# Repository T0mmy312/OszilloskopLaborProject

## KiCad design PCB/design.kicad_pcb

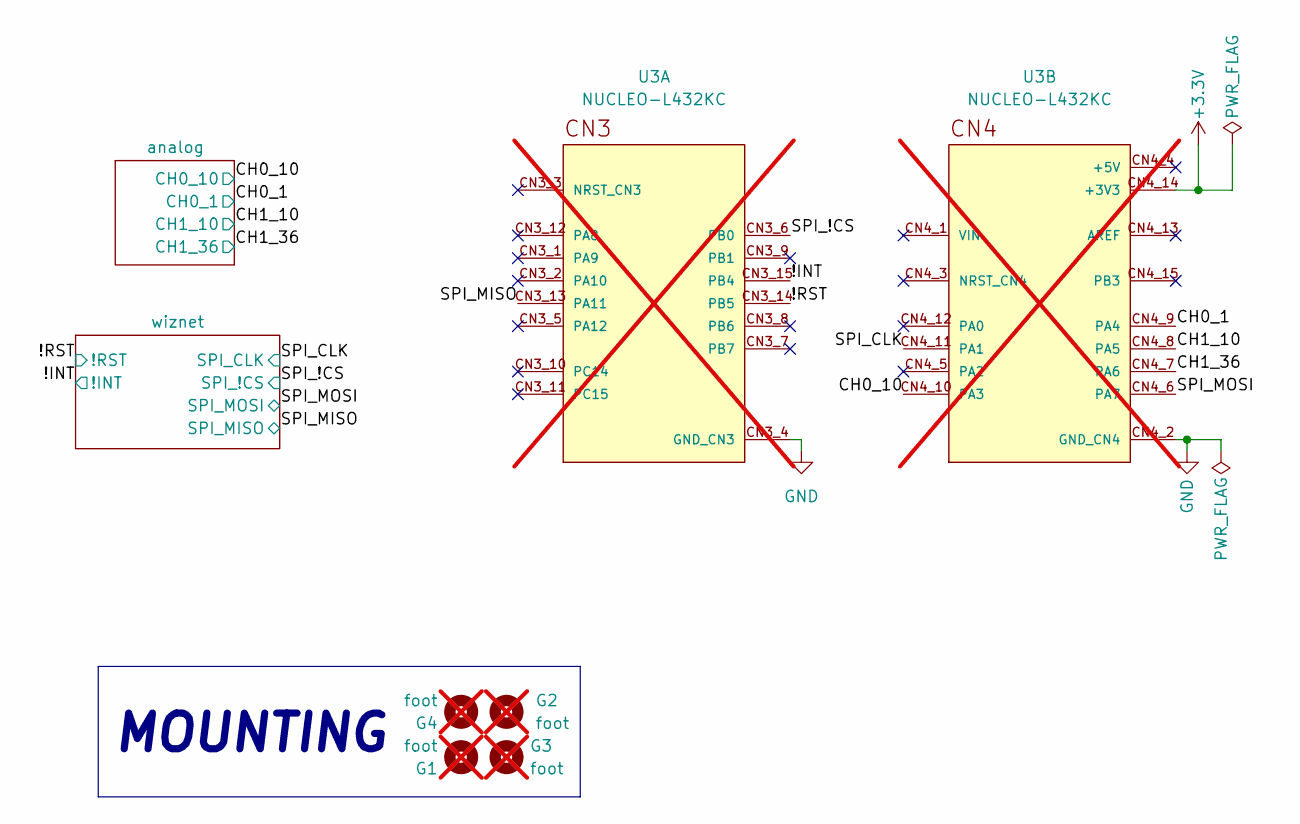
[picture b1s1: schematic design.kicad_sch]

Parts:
G1, G2, G3, G4: foot; G2009; not fitted
U3: NUCLEO-L432KC; PARTREV N/A; not fitted

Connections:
+3.3V: U3.CN4_14 (+3V3); also elsewhere on the board
/!INT: U3.CN3_15 (PB4); also elsewhere on the board
/!RST: U3.CN3_14 (PB5); also elsewhere on the board
/CH0_1: U3.CN4_9 (PA4); also elsewhere on the board
/CH0_10: U3.CN4_10 (PA3); also elsewhere on the board
/CH1_10: U3.CN4_8 (PA5); also elsewhere on the board
/CH1_36: U3.CN4_7 (PA6); also elsewhere on the board
/SPI_!CS: U3.CN3_6 (PB0); also elsewhere on the board
/SPI_CLK: U3.CN4_11 (PA1); also elsewhere on the board
/SPI_MISO: U3.CN3_13 (PA11); also elsewhere on the board
/SPI_MOSI: U3.CN4_6 (PA7); also elsewhere on the board
GND: U3.CN3_4 (GND_CN3), U3.CN4_2 (GND_CN4); also elsewhere on the board

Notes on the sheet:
MOUNTING

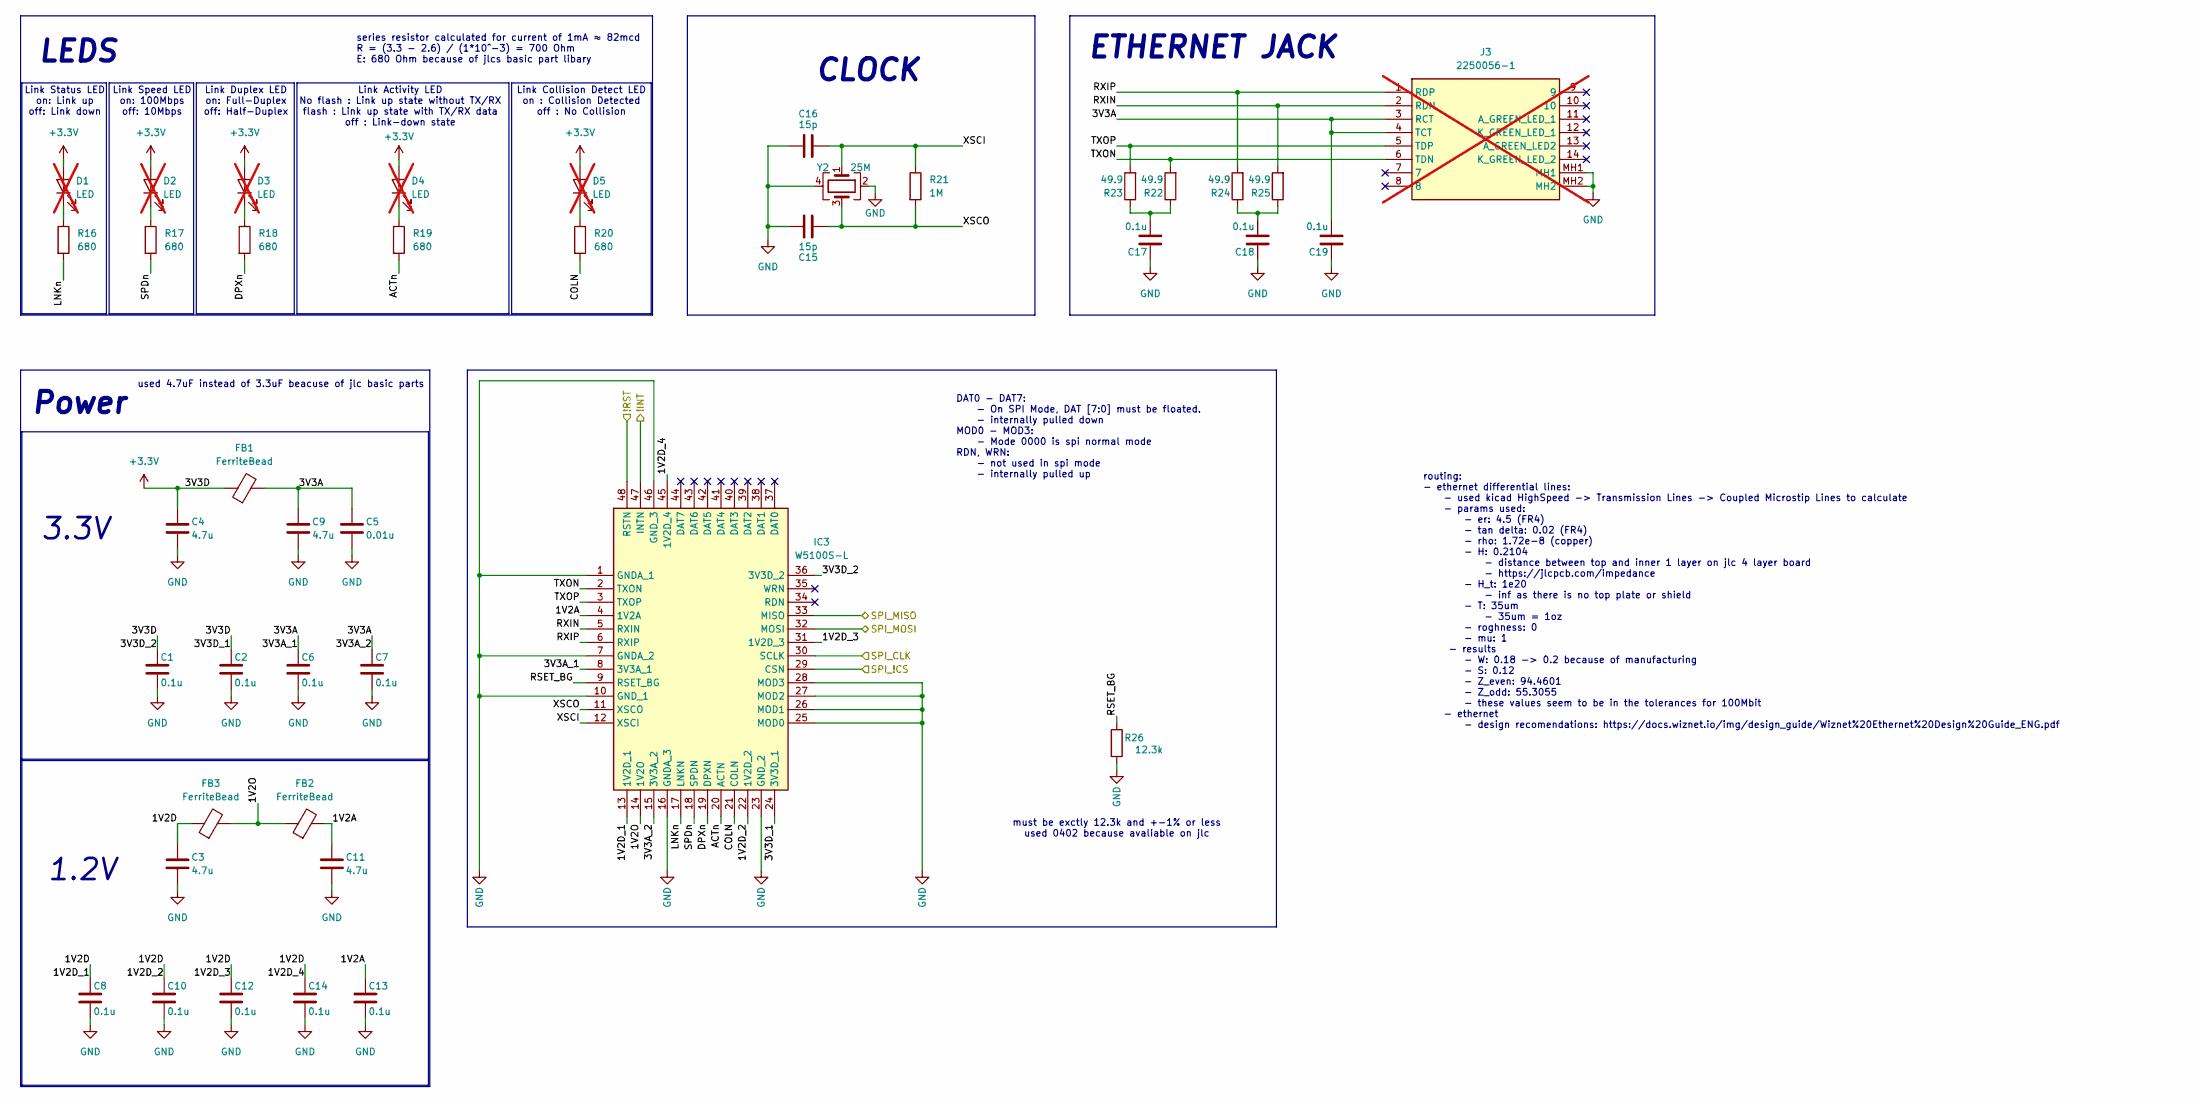
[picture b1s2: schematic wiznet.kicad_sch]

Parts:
C1, C2, C6, C7, C8, C10, C12, C13, C14, C17, C18, C19: 0.1u; C_0603_1608Metric; LCSC C14663
C3, C4, C9, C11: 4.7u; C_0603_1608Metric; LCSC C19666
C5: 0.01u; C_0603_1608Metric; LCSC C57112
C15, C16: 15p; C_0603_1608Metric; LCSC C1644
D1, D2, D3, D4, D5: LED; LED_0603_1608Metric; not fitted
FB1, FB2, FB3: FerriteBead; L_0603_1608Metric; LCSC C154133
IC3: W5100S-L; TQFP-48_7x7mm_P0.5mm; Manufacturer_Part_Number W5100S-L; LCSC C194673
J3: 2250056-1; 22500561; Mouser Part Number 530-2250056-1; not fitted
R16, R17, R18, R19, R20: 680; R_0603_1608Metric; LCSC C23228
R21: 1M; R_0603_1608Metric; LCSC C22935
R22, R23, R24, R25: 49.9; R_0603_1608Metric; LCSC C23184
R26: 12.3k; R_0402_1005Metric; LCSC C346621
Y2: 25M; Crystal_SMD_3225-4Pin_3.2x2.5mm; LCSC C9006

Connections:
+3.3V: C1.1, C2.1, C4.1, D1.2 (A), D2.2 (A), D3.2 (A), D4.2 (A), D5.2 (A), FB1.1, IC3.24 (3V3D_1), IC3.36 (3V3D_2); also elsewhere on the board
/!INT: IC3.47 (INTN); also elsewhere on the board
/!RST: IC3.48 (RSTN); also elsewhere on the board
/SPI_!CS: IC3.29 (CSN); also elsewhere on the board
/SPI_CLK: IC3.30 (SCLK); also elsewhere on the board
/SPI_MISO: IC3.33 (MISO); also elsewhere on the board
/SPI_MOSI: IC3.32 (MOSI); also elsewhere on the board
/wiznet/1V2A: C11.1, C13.1, FB2.2, IC3.4 (1V2A)
/wiznet/1V2D: C3.1, C8.1, C10.1, C12.1, C14.1, FB3.1, IC3.13 (1V2D_1), IC3.22 (1V2D_2), IC3.31 (1V2D_3), IC3.45 (1V2D_4)
/wiznet/1V2O: FB2.1, FB3.2, IC3.14 (1V2O)
/wiznet/3V3A: C5.1, C6.1, C7.1, C9.1, C19.2, FB1.2, IC3.8 (3V3A_1), IC3.15 (3V3A_2), J3.3 (RCT), J3.4 (TCT)
/wiznet/ACTn: IC3.20 (ACTN), R19.2
/wiznet/COLN: IC3.21 (COLN), R20.2
/wiznet/DPXn: IC3.19 (DPXN), R18.2
/wiznet/LNKn: IC3.17 (LNKN), R16.2
/wiznet/RSET_BG: IC3.9 (RSET_BG), R26.1
/wiznet/RXIN: IC3.5 (RXIN), J3.2 (RDN), R25.2
/wiznet/RXIP: IC3.6 (RXIP), J3.1 (RDP), R24.2
/wiznet/SPDn: IC3.18 (SPDN), R17.2
/wiznet/TXON: IC3.2 (TXON), J3.6 (TDN), R22.2
/wiznet/TXOP: IC3.3 (TXOP), J3.5 (TDP), R23.2
/wiznet/XSCI: C16.1, IC3.12 (XSCI), R21.1, Y2.1
/wiznet/XSCO: C15.2, IC3.11 (XSCO), R21.2, Y2.3
GND: C1.2, C2.2, C3.2, C4.2, C5.2, C6.2, C7.2, C8.2, C9.2, C10.2, C11.2, C12.2, C13.2, C14.2, C15.1, C16.2, C17.1, C18.1, C19.1, IC3.1 (GNDA_1), IC3.7 (GNDA_2), IC3.10 (GND_1), IC3.16 (GNDA_3), IC3.23 (GND_2), IC3.25 (MOD0), IC3.26 (MOD1), IC3.27 (MOD2), IC3.28 (MOD3), IC3.46 (GND_3), J3.MH1, J3.MH2, R26.2, Y2.2, Y2.4; also elsewhere on the board
unnamed: C17.2, R22.1, R23.1
unnamed: C18.2, R24.1, R25.1
unnamed: D1.1 (K), R16.1
unnamed: D2.1 (K), R17.1
unnamed: D3.1 (K), R18.1
unnamed: D4.1 (K), R19.1
unnamed: D5.1 (K), R20.1

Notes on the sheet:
LEDS
1.2V
Link Speed LED on: 100Mbps off: 10Mbps
DAT0 - DAT7: - On SPI Mode, DAT [7:0] must be floated. - internally pulled down MOD0 - MOD3: - Mode 0000 is spi normal mode RDN, WRN: - not used in spi mode - internally pulled up
ETHERNET JACK
3.3V
Link Collision Detect LED on : Collision Detected off : No Collision
must be exctly 12.3k and +-1% or less used 0402 because avaliable on jlc
series resistor calculated for current of 1mA ≈ 82mcd R = (3.3 - 2.6) / (1*10^-3) = 700 Ohm E: 680 Ohm because of jlcs basic part libary
Link Duplex LED on: Full-Duplex off: Half-Duplex
Link Status LED on: Link up off: Link down
used 4.7uF instead of 3.3uF beacuse of jlc basic parts
routing: - ethernet differential lines: - used kicad HighSpeed -> Transmission Lines -> Coupled Microstip Lines to calculate - params used: - er: 4.5 (FR4) - tan delta: 0.02 (FR4) - rho: 1.72e-8 (copper) - H: 0.2104 - distance between top and inner 1 layer on jlc 4 layer board - https://jlcpcb.com/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
Link Activity LED No flash : Link up state without TX/RX flash : Link up state with TX/RX data off : Link-down state
Power
CLOCK

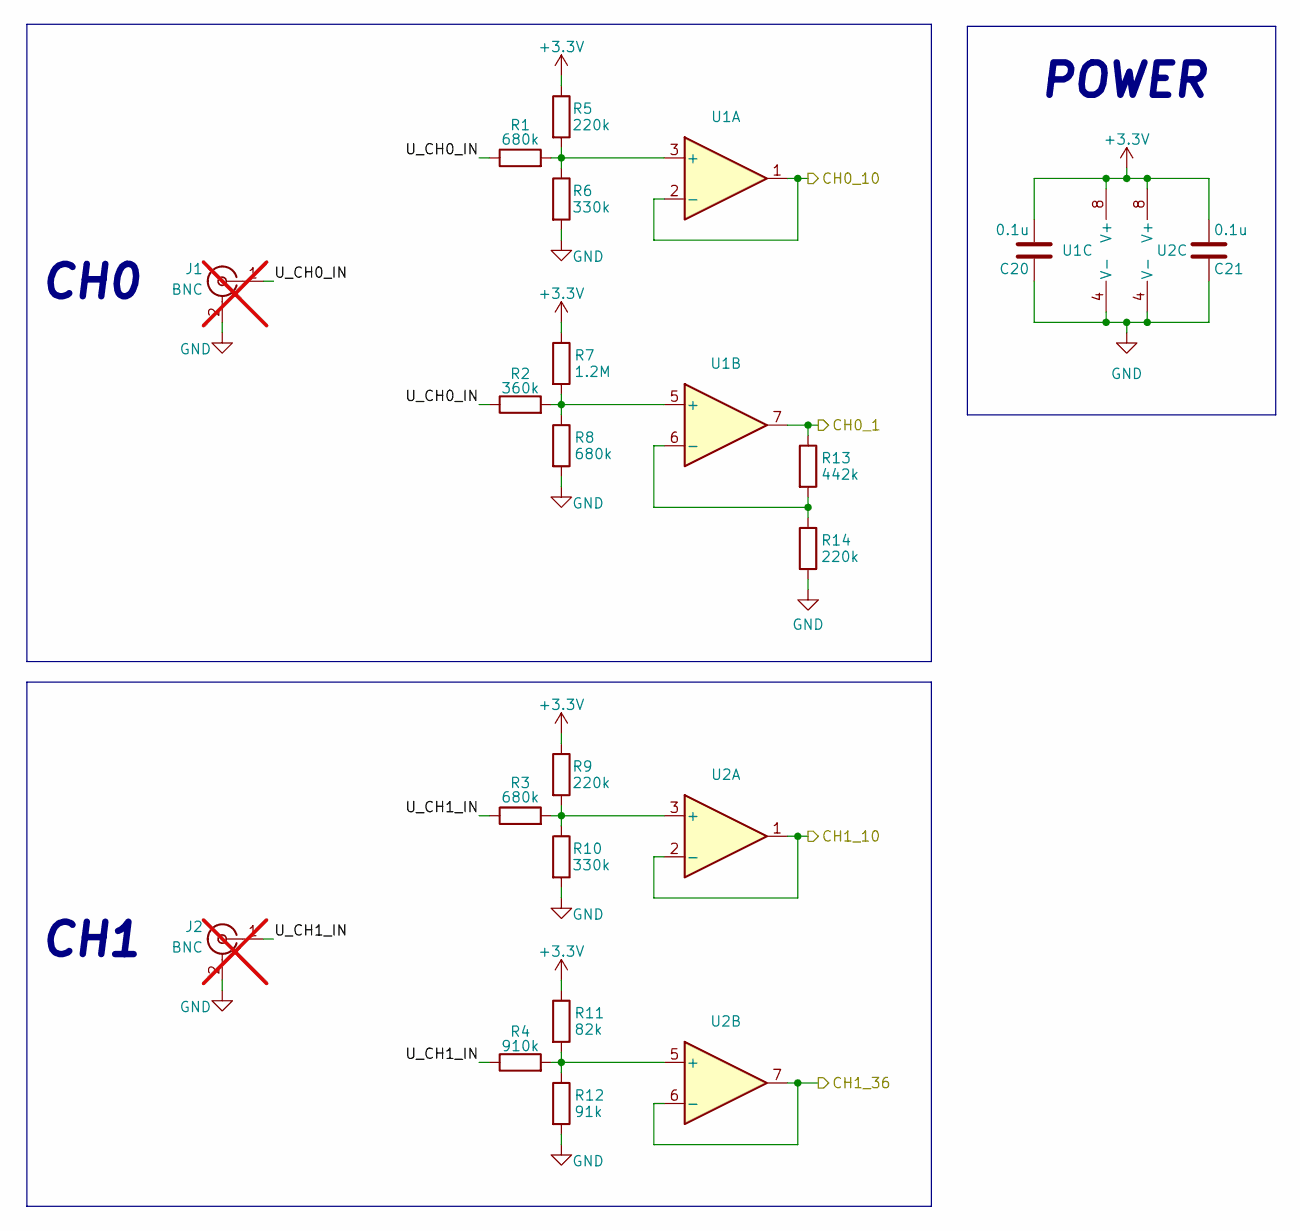
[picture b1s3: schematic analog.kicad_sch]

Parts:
C20, C21: 0.1u; C_0603_1608Metric; LCSC C14663
J1, J2: BNC; 731713150; not fitted
R1, R3, R8: 680k; R_0603_1608Metric; LCSC C25822
R2: 360k; R_0603_1608Metric; LCSC C23146
R4: 910k; R_0603_1608Metric; LCSC C23263
R5, R9, R14: 220k; R_0603_1608Metric; LCSC C22961
R6, R10: 330k; R_0603_1608Metric; LCSC C23137
R7: 1.2M; R_0603_1608Metric; LCSC C13315
R11: 82k; R_0603_1608Metric; LCSC C23254
R12: 91k; R_0603_1608Metric; LCSC C23265
R13: 442k; R_0603_1608Metric; LCSC C23175
U1, U2: MCP6002-xMC; SOIC-8_3.9x4.9mm_P1.27mm; LCSC C7377

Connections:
+3.3V: C20.2, C21.2, R5.1, R7.1, R9.1, R11.1, U1.8 (V+), U2.8 (V+); also elsewhere on the board
/CH0_1: R13.1, U1.7; also elsewhere on the board
/CH0_10: U1.1, U1.2 (-); also elsewhere on the board
/CH1_10: U2.1, U2.2 (-); also elsewhere on the board
/CH1_36: U2.6 (-), U2.7; also elsewhere on the board
/analog/U_CH0_IN: J1.1 (In), R1.1, R2.1
/analog/U_CH1_IN: J2.1 (In), R3.1, R4.1
GND: C20.1, C21.1, J1.2 (Ext), J2.2 (Ext), R6.2, R8.2, R10.2, R12.2, R14.2, U1.4 (V-), U2.4 (V-); also elsewhere on the board
unnamed: R1.2, R5.2, R6.1, U1.3 (+)
unnamed: R2.2, R7.2, R8.1, U1.5 (+)
unnamed: R13.2, R14.1, U1.6 (-)
unnamed: R3.2, R9.2, R10.1, U2.3 (+)
unnamed: R4.2, R11.2, R12.1, U2.5 (+)

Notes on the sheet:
CH0
CH1
POWER

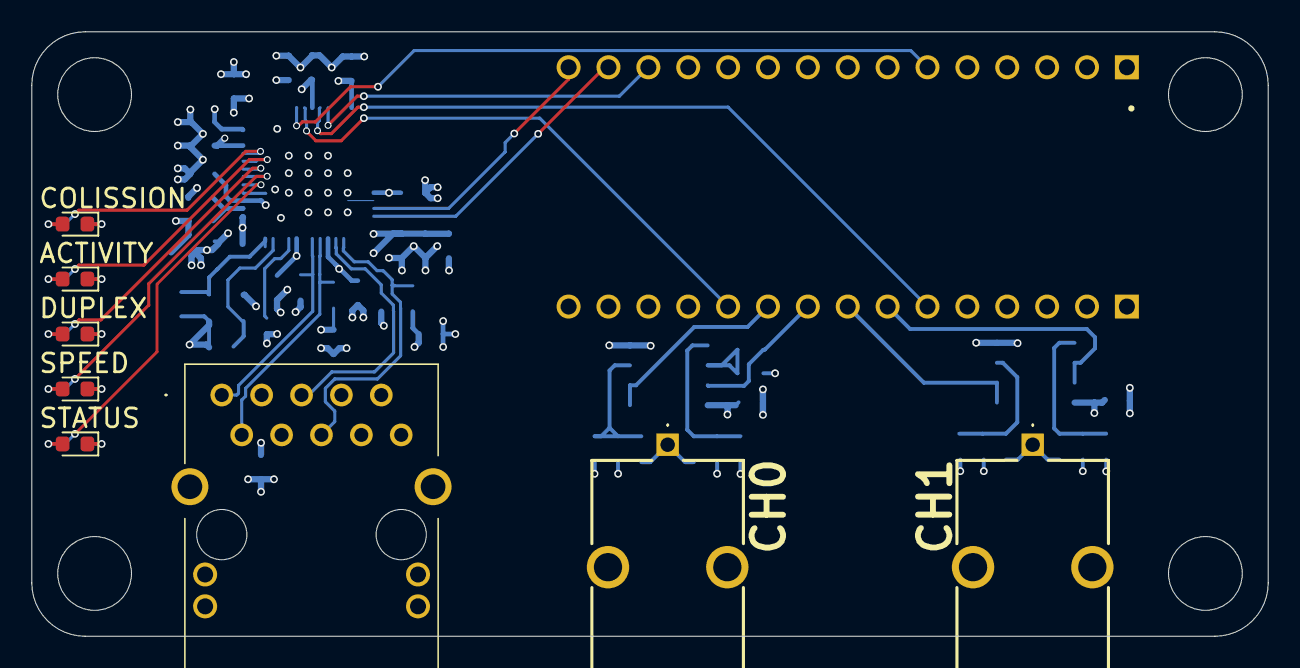
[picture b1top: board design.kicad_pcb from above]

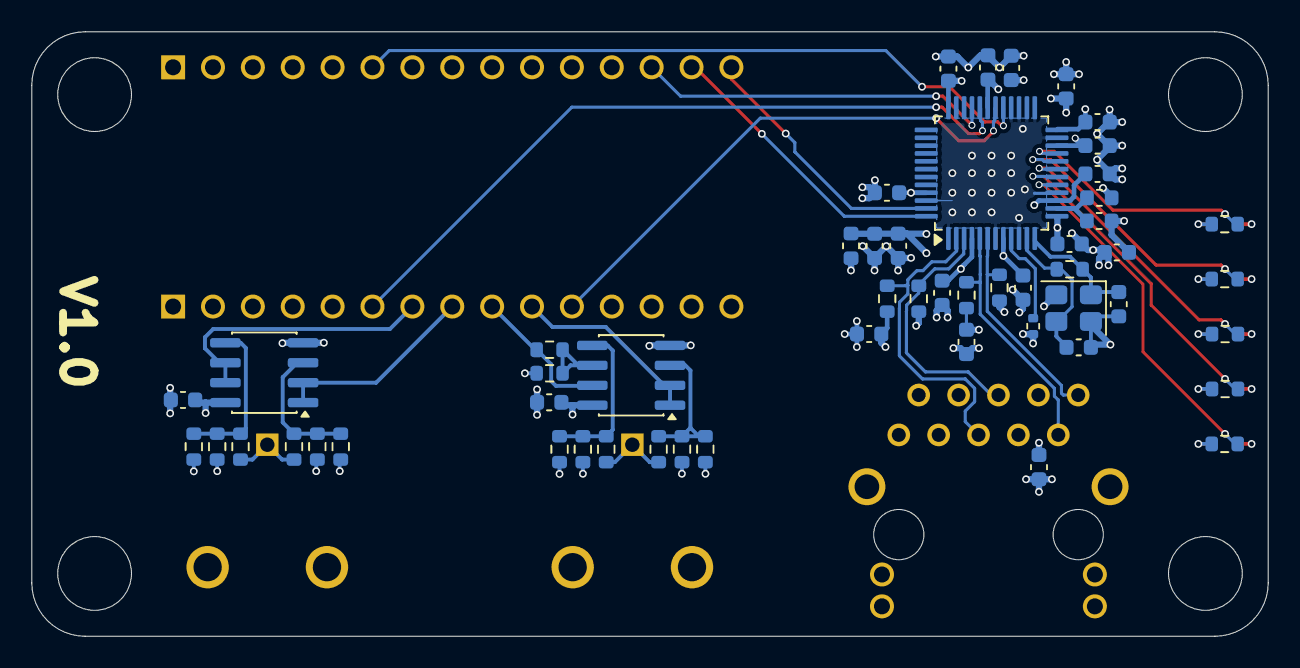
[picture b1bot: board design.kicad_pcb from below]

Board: 4 copper layers, 78.8 x 38.5 mm, 66 parts (53 on the bottom side), 42 nets.

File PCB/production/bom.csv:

Designator,Footprint,Quantity,Value,LCSC Part #
"C1, C10, C12, C13, C14, C17, C18, C19, C2, C20, C21, C6, C7, C8",0603,14,0.1u,C14663
"C11, C3, C4, C9",0603,4,4.7u,C19666
"C15, C16",0603,2,15p,C1644
C5,0603,1,0.01u,C57112
"FB1, FB2, FB3",0603,3,FerriteBead,C154133
IC3,TQFP-48_7x7mm_P0.5mm,1,W5100S-L,C194673
"R1, R3, R8",0603,3,680k,C25822
"R10, R6",0603,2,330k,C23137
R11,0603,1,82k, C23254
R12,0603,1,91k,C23265
R13,0603,1,442k,C23175
"R14, R5, R9",0603,3,220k, C22961
"R16, R17, R18, R19, R20",0603,5,680,C23228
R2,0603,1,360k,C23146
R21,0603,1,1M,C22935
"R22, R23, R24, R25",0603,4,49.9,C23184
R26,0402,1,12.3k,C346621
R4,0603,1,910k,C23263
R7,0603,1,1.2M, C13315
"U1, U2",SOIC-8_3.9x4.9mm_P1.27mm,2,MCP6002-xMC,C7377
Y2,Crystal_SMD_3225-4Pin_3.2x2.5mm,1,25M,C9006

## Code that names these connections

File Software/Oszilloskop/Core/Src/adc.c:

/* USER CODE BEGIN Header */
/**
  ******************************************************************************
  * @file    adc.c
  * @brief   This file provides code for the configuration
  *          of the ADC instances.
  ******************************************************************************
  * @attention
  *
  * Copyright (c) 2025 STMicroelectronics.
  * All rights reserved.
  *
  * This software is licensed under terms that can be found in the LICENSE file
  * in the root directory of this software component.
  * If no LICENSE file comes with this software, it is provided AS-IS.
  *
  ******************************************************************************
  */
/* USER CODE END Header */
/* Includes ------------------------------------------------------------------*/
#include "adc.h"

/* USER CODE BEGIN 0 */

/* USER CODE END 0 */

ADC_HandleTypeDef hadc1;
DMA_HandleTypeDef hdma_adc1;

/* ADC1 init function */
void MX_ADC1_Init(void)
{

  /* USER CODE BEGIN ADC1_Init 0 */

  /* USER CODE END ADC1_Init 0 */

  ADC_ChannelConfTypeDef sConfig = {0};

  /* USER CODE BEGIN ADC1_Init 1 */

  /* USER CODE END ADC1_Init 1 */

  /** Common config
  */
  hadc1.Instance = ADC1;
  hadc1.Init.ClockPrescaler = ADC_CLOCK_ASYNC_DIV64;
  hadc1.Init.Resolution = ADC_RESOLUTION_12B;
  hadc1.Init.DataAlign = ADC_DATAALIGN_RIGHT;
  hadc1.Init.ScanConvMode = ADC_SCAN_ENABLE;
  hadc1.Init.EOCSelection = ADC_EOC_SEQ_CONV;
  hadc1.Init.LowPowerAutoWait = DISABLE;
  hadc1.Init.ContinuousConvMode = ENABLE;
  hadc1.Init.NbrOfConversion = 4;
  hadc1.Init.DiscontinuousConvMode = DISABLE;
  hadc1.Init.ExternalTrigConv = ADC_SOFTWARE_START;
  hadc1.Init.ExternalTrigConvEdge = ADC_EXTERNALTRIGCONVEDGE_NONE;
  hadc1.Init.DMAContinuousRequests = ENABLE;
  hadc1.Init.Overrun = ADC_OVR_DATA_PRESERVED;
  hadc1.Init.OversamplingMode = DISABLE;
  if (HAL_ADC_Init(&hadc1) != HAL_OK)
  {
    Error_Handler();
  }

  /** Configure Regular Channel
  */
  sConfig.Channel = ADC_CHANNEL_8;
  sConfig.Rank = ADC_REGULAR_RANK_1;
  sConfig.SamplingTime = ADC_SAMPLETIME_12CYCLES_5;
  sConfig.SingleDiff = ADC_SINGLE_ENDED;
  sConfig.OffsetNumber = ADC_OFFSET_NONE;
  sConfig.Offset = 0;
  if (HAL_ADC_ConfigChannel(&hadc1, &sConfig) != HAL_OK)
  {
    Error_Handler();
  }

  /** Configure Regular Channel
  */
  sConfig.Channel = ADC_CHANNEL_9;
  sConfig.Rank = ADC_REGULAR_RANK_2;
  if (HAL_ADC_ConfigChannel(&hadc1, &sConfig) != HAL_OK)
  {
    Error_Handler();
  }

  /** Configure Regular Channel
  */
  sConfig.Channel = ADC_CHANNEL_10;
  sConfig.Rank = ADC_REGULAR_RANK_3;
  if (HAL_ADC_ConfigChannel(&hadc1, &sConfig) != HAL_OK)
  {
    Error_Handler();
  }

  /** Configure Regular Channel
  */
  sConfig.Channel = ADC_CHANNEL_11;
  sConfig.Rank = ADC_REGULAR_RANK_4;
  if (HAL_ADC_ConfigChannel(&hadc1, &sConfig) != HAL_OK)
  {
    Error_Handler();
  }
  /* USER CODE BEGIN ADC1_Init 2 */

  /* USER CODE END ADC1_Init 2 */

}

void HAL_ADC_MspInit(ADC_HandleTypeDef* adcHandle)
{

  GPIO_InitTypeDef GPIO_InitStruct = {0};
  RCC_PeriphCLKInitTypeDef PeriphClkInit = {0};
  if(adcHandle->Instance==ADC1)
  {
  /* USER CODE BEGIN ADC1_MspInit 0 */

  /* USER CODE END ADC1_MspInit 0 */

  /** Initializes the peripherals clock
  */
    PeriphClkInit.PeriphClockSelection = RCC_PERIPHCLK_ADC;
    PeriphClkInit.AdcClockSelection = RCC_ADCCLKSOURCE_PLLSAI1;
    PeriphClkInit.PLLSAI1.PLLSAI1Source = RCC_PLLSOURCE_MSI;
    PeriphClkInit.PLLSAI1.PLLSAI1M = 1;
    PeriphClkInit.PLLSAI1.PLLSAI1N = 16;
    PeriphClkInit.PLLSAI1.PLLSAI1P = RCC_PLLP_DIV7;
    PeriphClkInit.PLLSAI1.PLLSAI1Q = RCC_PLLQ_DIV2;
    PeriphClkInit.PLLSAI1.PLLSAI1R = RCC_PLLR_DIV2;
    PeriphClkInit.PLLSAI1.PLLSAI1ClockOut = RCC_PLLSAI1_ADC1CLK;
    if (HAL_RCCEx_PeriphCLKConfig(&PeriphClkInit) != HAL_OK)
    {
      Error_Handler();
    }

    /* ADC1 clock enable */
    __HAL_RCC_ADC_CLK_ENABLE();

    __HAL_RCC_GPIOA_CLK_ENABLE();
    /**ADC1 GPIO Configuration
    PA3     ------> ADC1_IN8
    PA4     ------> ADC1_IN9
    PA5     ------> ADC1_IN10
    PA6     ------> ADC1_IN11
    */
    GPIO_InitStruct.Pin = GPIO_PIN_3|GPIO_PIN_4|GPIO_PIN_5|GPIO_PIN_6;
    GPIO_InitStruct.Mode = GPIO_MODE_ANALOG_ADC_CONTROL;
    GPIO_InitStruct.Pull = GPIO_NOPULL;
    HAL_GPIO_Init(GPIOA, &GPIO_InitStruct);

    /* ADC1 DMA Init */
    /* ADC1 Init */
    hdma_adc1.Instance = DMA1_Channel1;
    hdma_adc1.Init.Request = DMA_REQUEST_0;
    hdma_adc1.Init.Direction = DMA_PERIPH_TO_MEMORY;
    hdma_adc1.Init.PeriphInc = DMA_PINC_DISABLE;
    hdma_adc1.Init.MemInc = DMA_MINC_ENABLE;
    hdma_adc1.Init.PeriphDataAlignment = DMA_PDATAALIGN_HALFWORD;
    hdma_adc1.Init.MemDataAlignment = DMA_MDATAALIGN_HALFWORD;
    hdma_adc1.Init.Mode = DMA_CIRCULAR;
    hdma_adc1.Init.Priority = DMA_PRIORITY_VERY_HIGH;
    if (HAL_DMA_Init(&hdma_adc1) != HAL_OK)
    {
      Error_Handler();
    }

    __HAL_LINKDMA(adcHandle,DMA_Handle,hdma_adc1);

    /* ADC1 interrupt Init */
    HAL_NVIC_SetPriority(ADC1_IRQn, 0, 0);
    HAL_NVIC_EnableIRQ(ADC1_IRQn);
  /* USER CODE BEGIN ADC1_MspInit 1 */

  /* USER CODE END ADC1_MspInit 1 */
  }
}

void HAL_ADC_MspDeInit(ADC_HandleTypeDef* adcHandle)
{

  if(adcHandle->Instance==ADC1)
  {
  /* USER CODE BEGIN ADC1_MspDeInit 0 */

  /* USER CODE END ADC1_MspDeInit 0 */
    /* Peripheral clock disable */
    __HAL_RCC_ADC_CLK_DISABLE();

    /**ADC1 GPIO Configuration
    PA3     ------> ADC1_IN8
    PA4     ------> ADC1_IN9
    PA5     ------> ADC1_IN10
    PA6     ------> ADC1_IN11
    */
    HAL_GPIO_DeInit(GPIOA, GPIO_PIN_3|GPIO_PIN_4|GPIO_PIN_5|GPIO_PIN_6);

    /* ADC1 DMA DeInit */
    HAL_DMA_DeInit(adcHandle->DMA_Handle);

    /* ADC1 interrupt Deinit */
    HAL_NVIC_DisableIRQ(ADC1_IRQn);
  /* USER CODE BEGIN ADC1_MspDeInit 1 */

  /* USER CODE END ADC1_MspDeInit 1 */
  }
}

/* USER CODE BEGIN 1 */

/* USER CODE END 1 */

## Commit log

2025-11-28 Added Webapp
2025-11-28 add pcb
2025-11-28 revert footprints back to original
2025-12-05 lock board edge
2025-12-05 added lots of webapp stuff
2025-12-12 add better ground vias; rename footprints and 3d-models
2025-12-12 add .kicad_prl files
2025-12-12 remove unneeded pin; update invalid footprint
2025-12-12 resolve symbol, footprint issues
2025-12-12 change leds to mouser
2025-12-15 resolve footprint issues
2025-12-15 make vias bigger than 0.3mm/0.45mm
2025-12-16 add V1.0 silkscreen text
2025-12-16 update production files
2025-12-16 add channel silkscreen labels
